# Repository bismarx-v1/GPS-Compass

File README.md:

# GPS Compass
this compass points to a specific locations a user defines, it has two pointers, one for distance and another one for the specified locations

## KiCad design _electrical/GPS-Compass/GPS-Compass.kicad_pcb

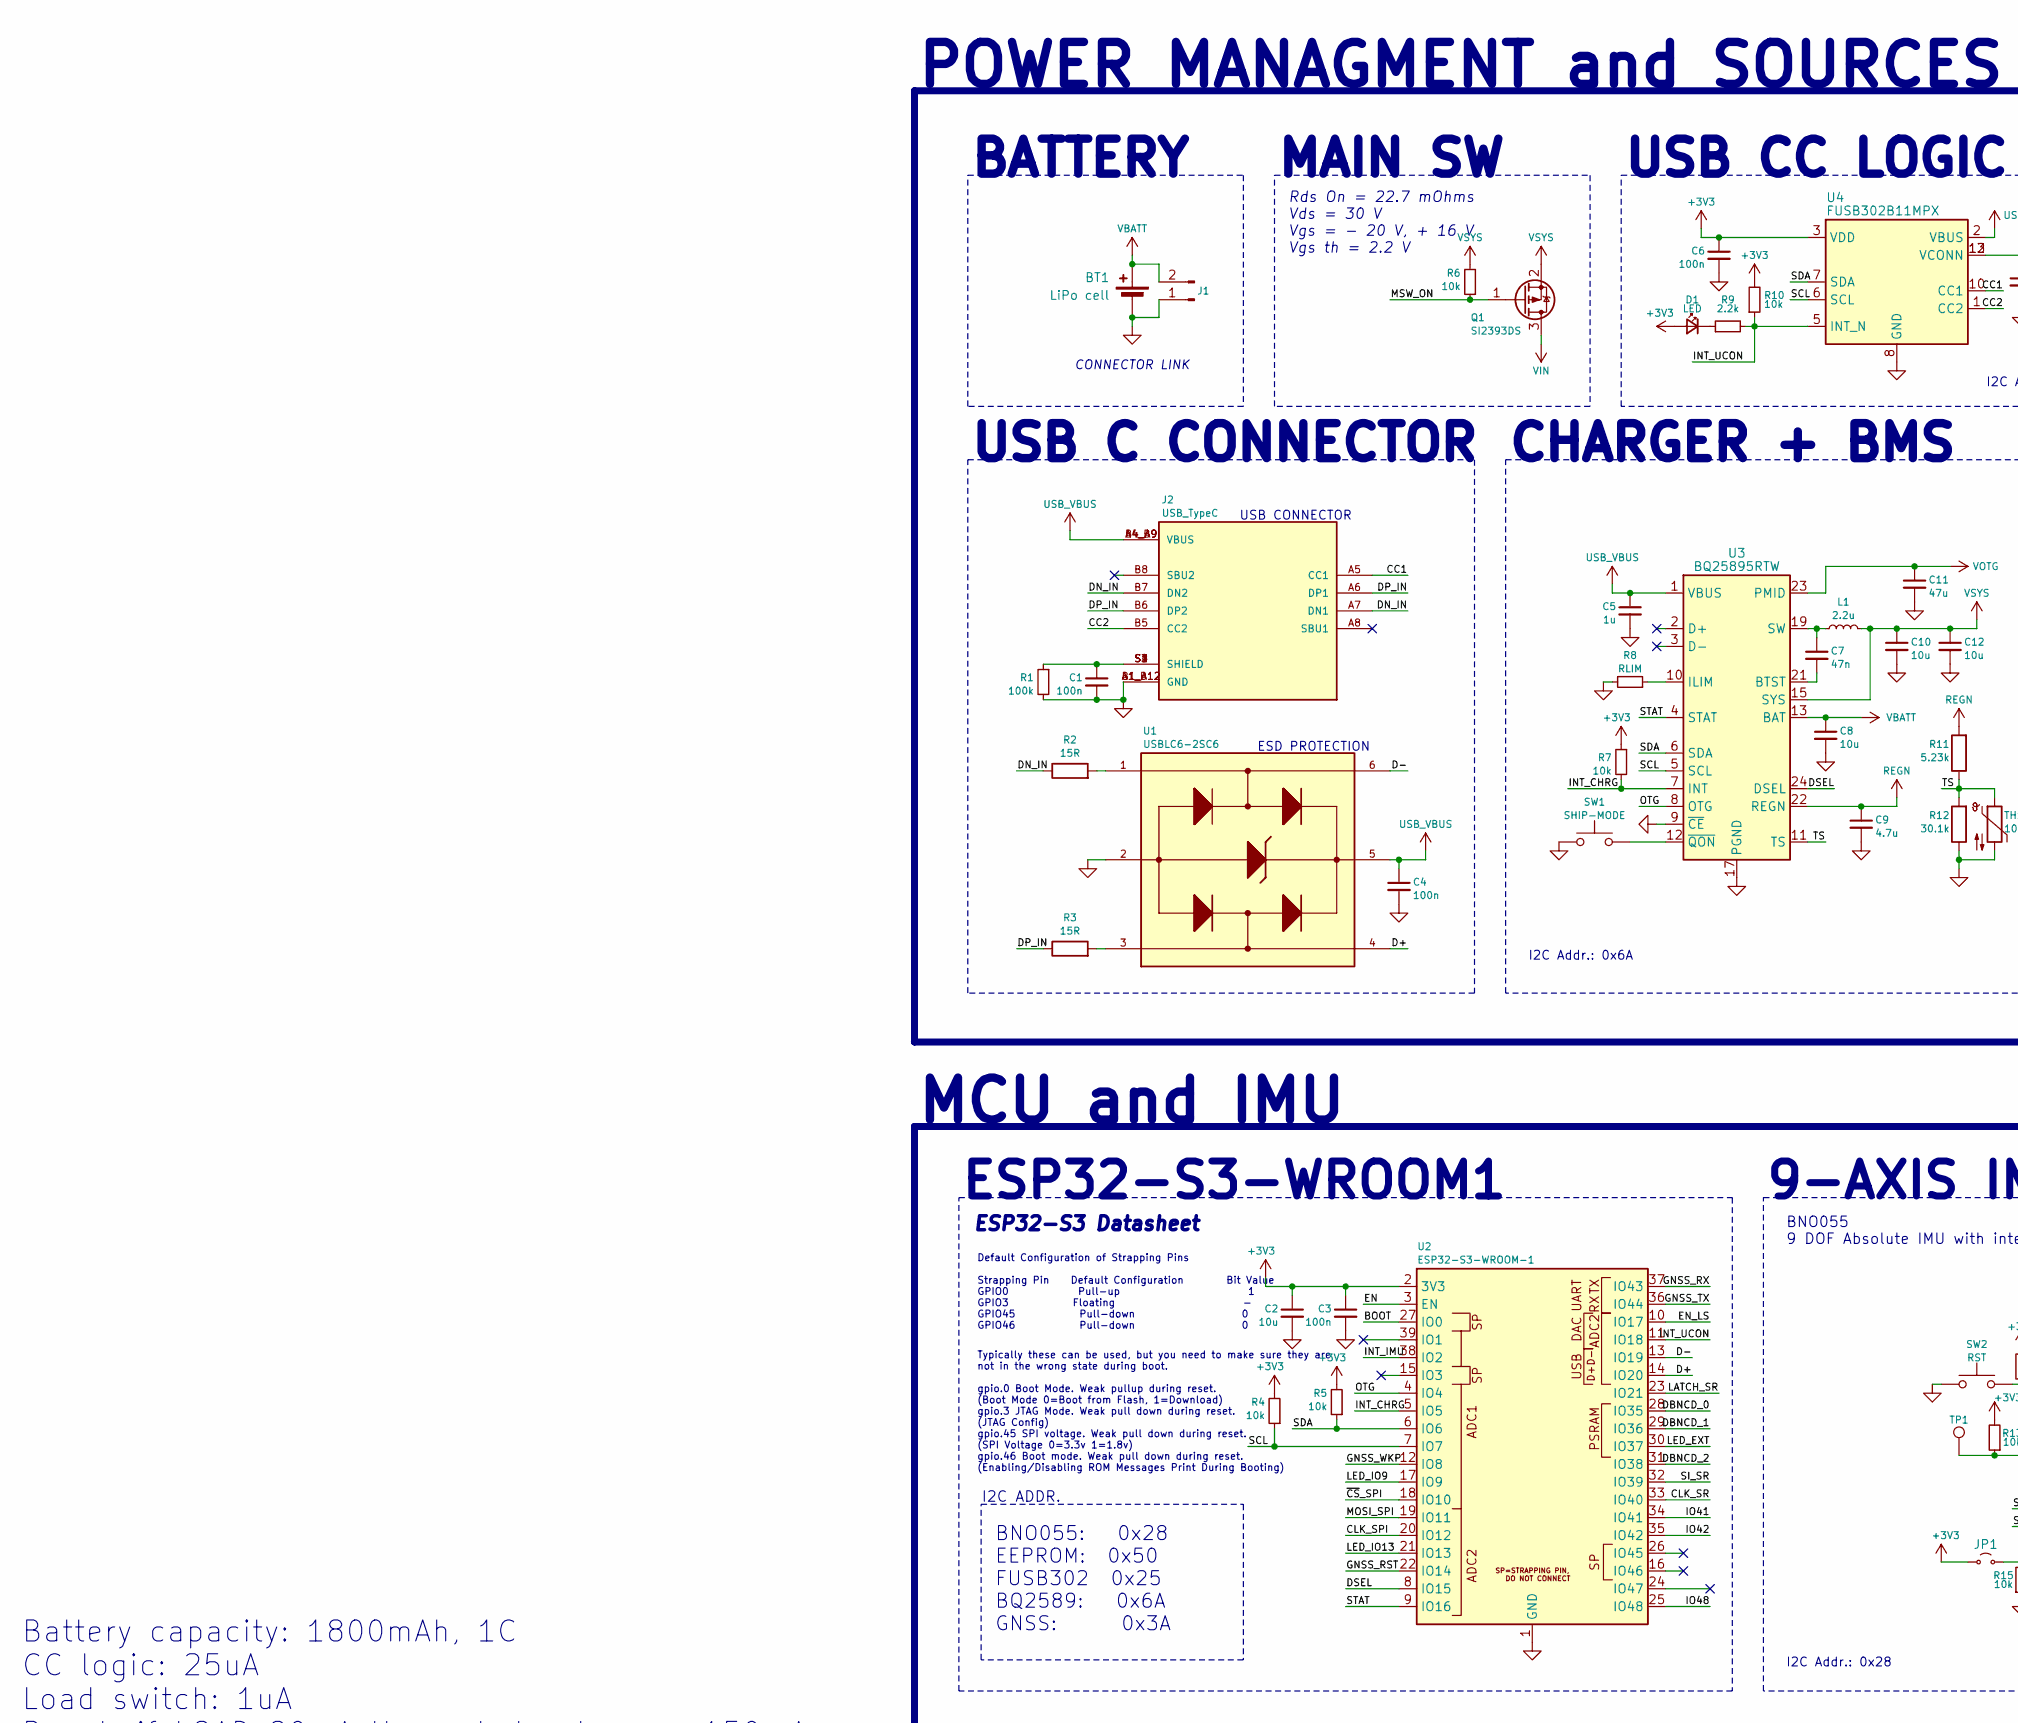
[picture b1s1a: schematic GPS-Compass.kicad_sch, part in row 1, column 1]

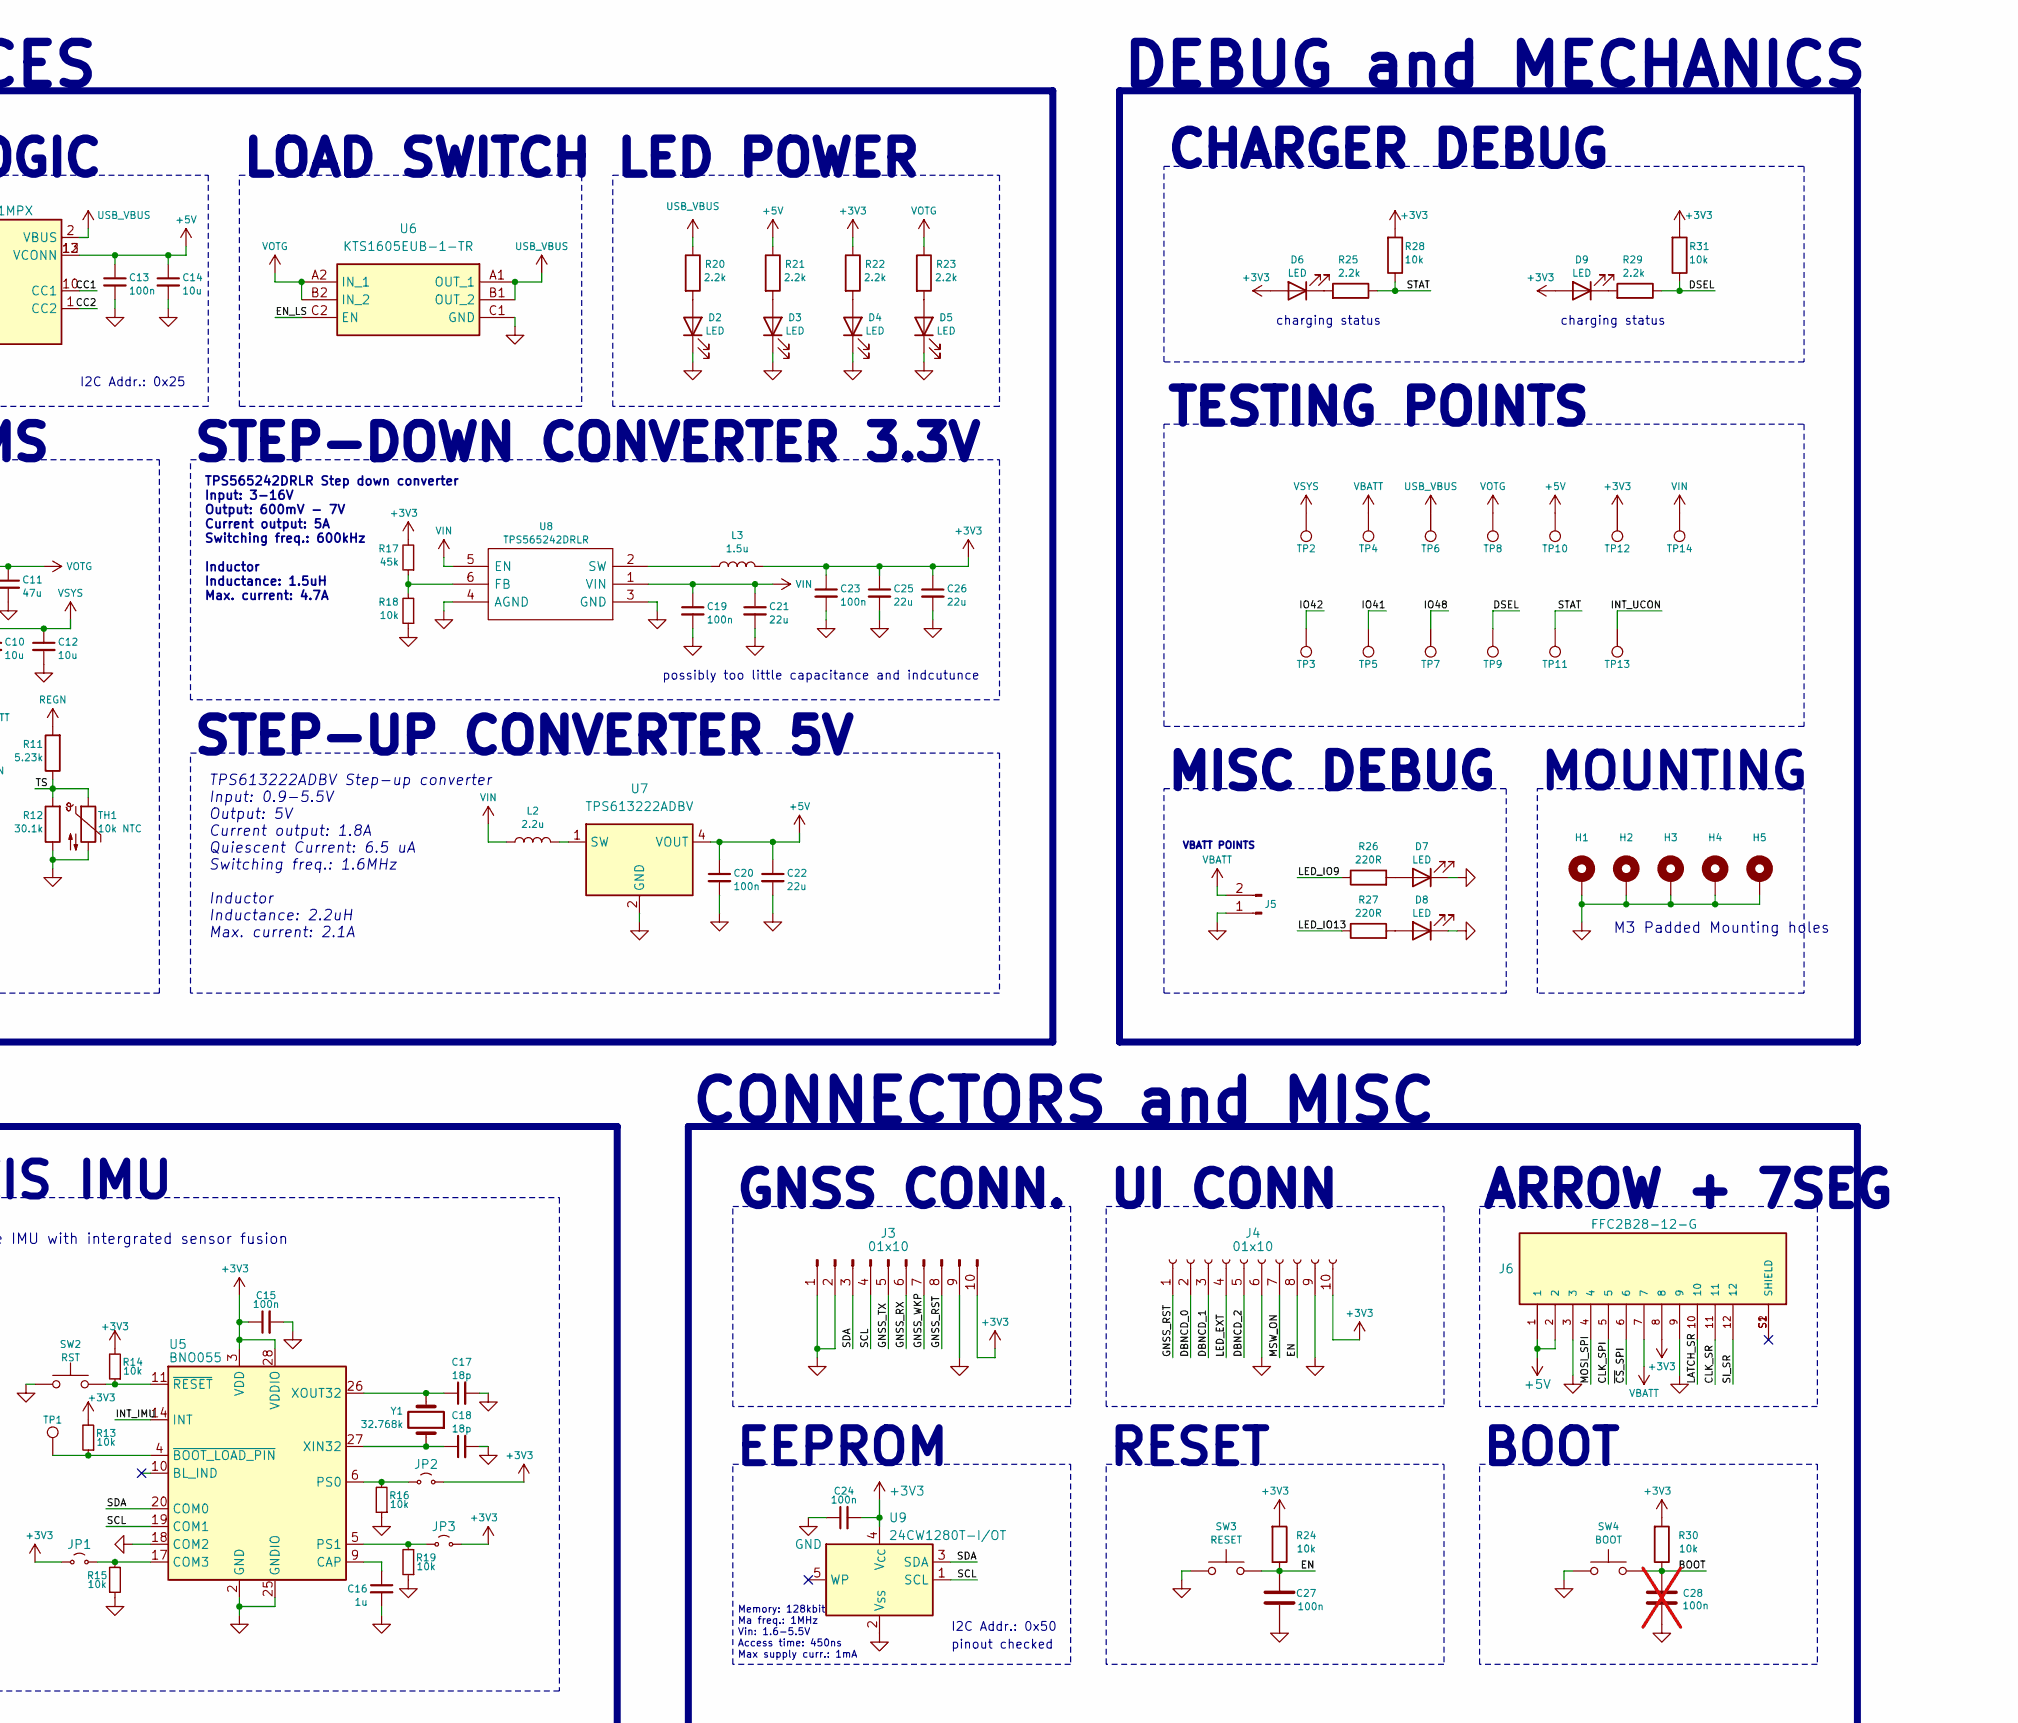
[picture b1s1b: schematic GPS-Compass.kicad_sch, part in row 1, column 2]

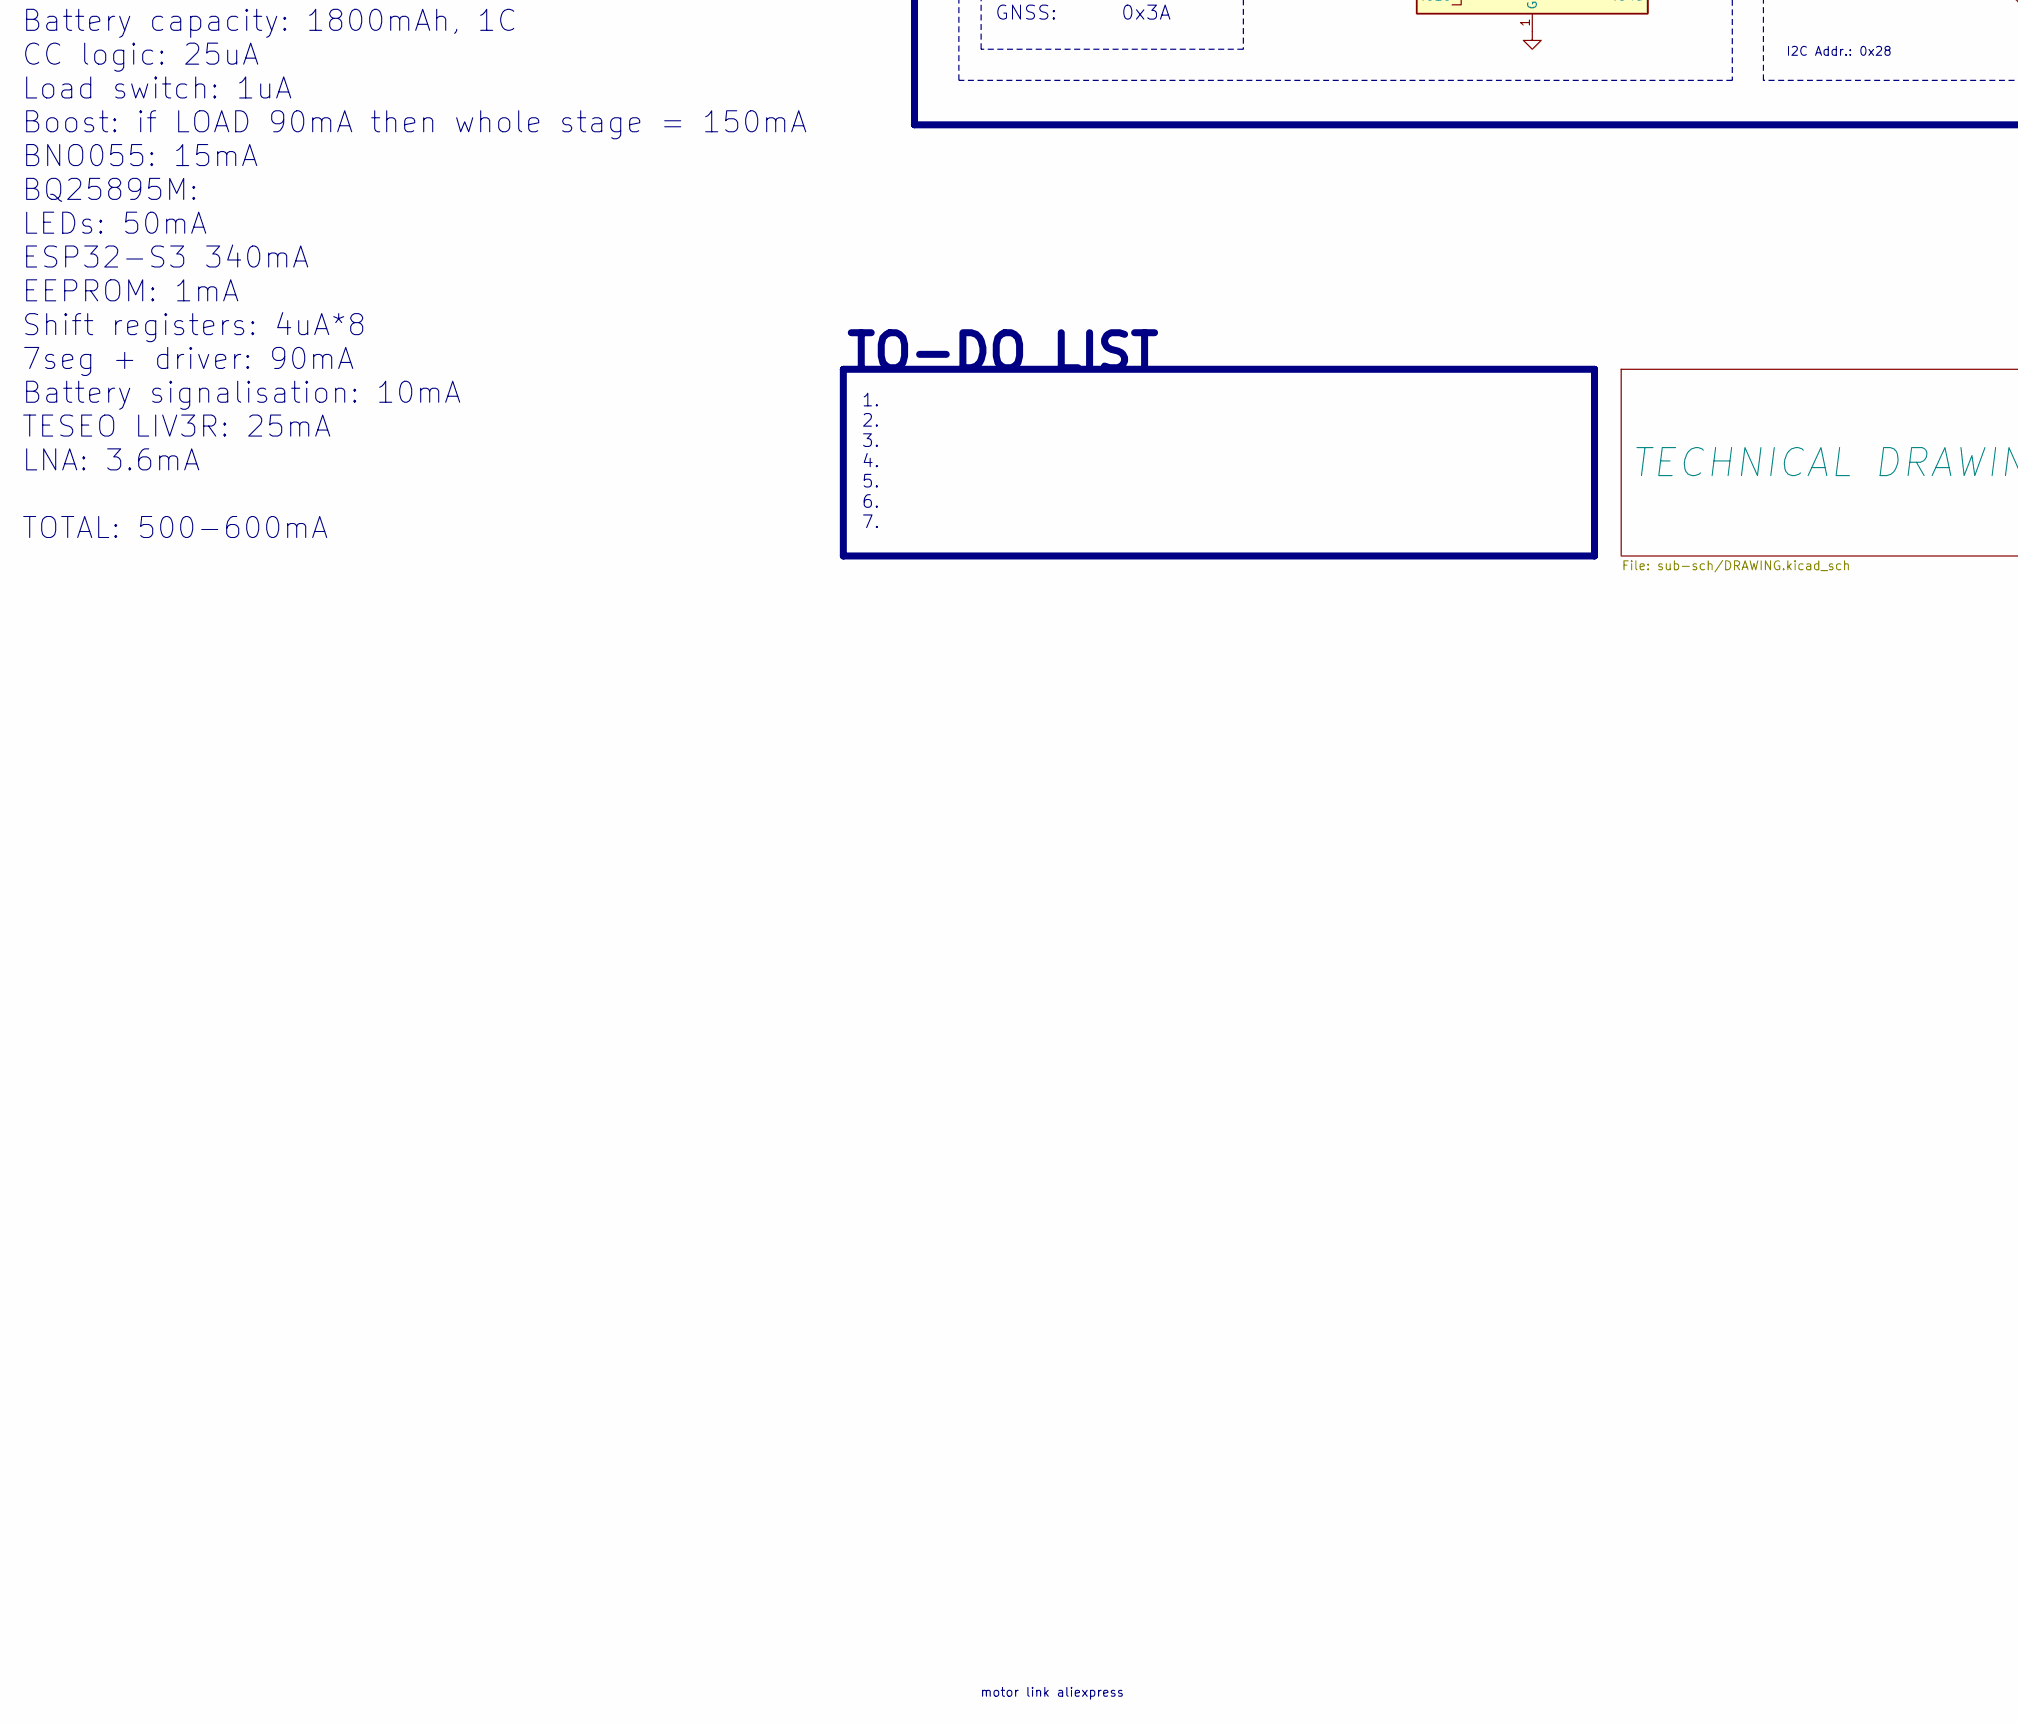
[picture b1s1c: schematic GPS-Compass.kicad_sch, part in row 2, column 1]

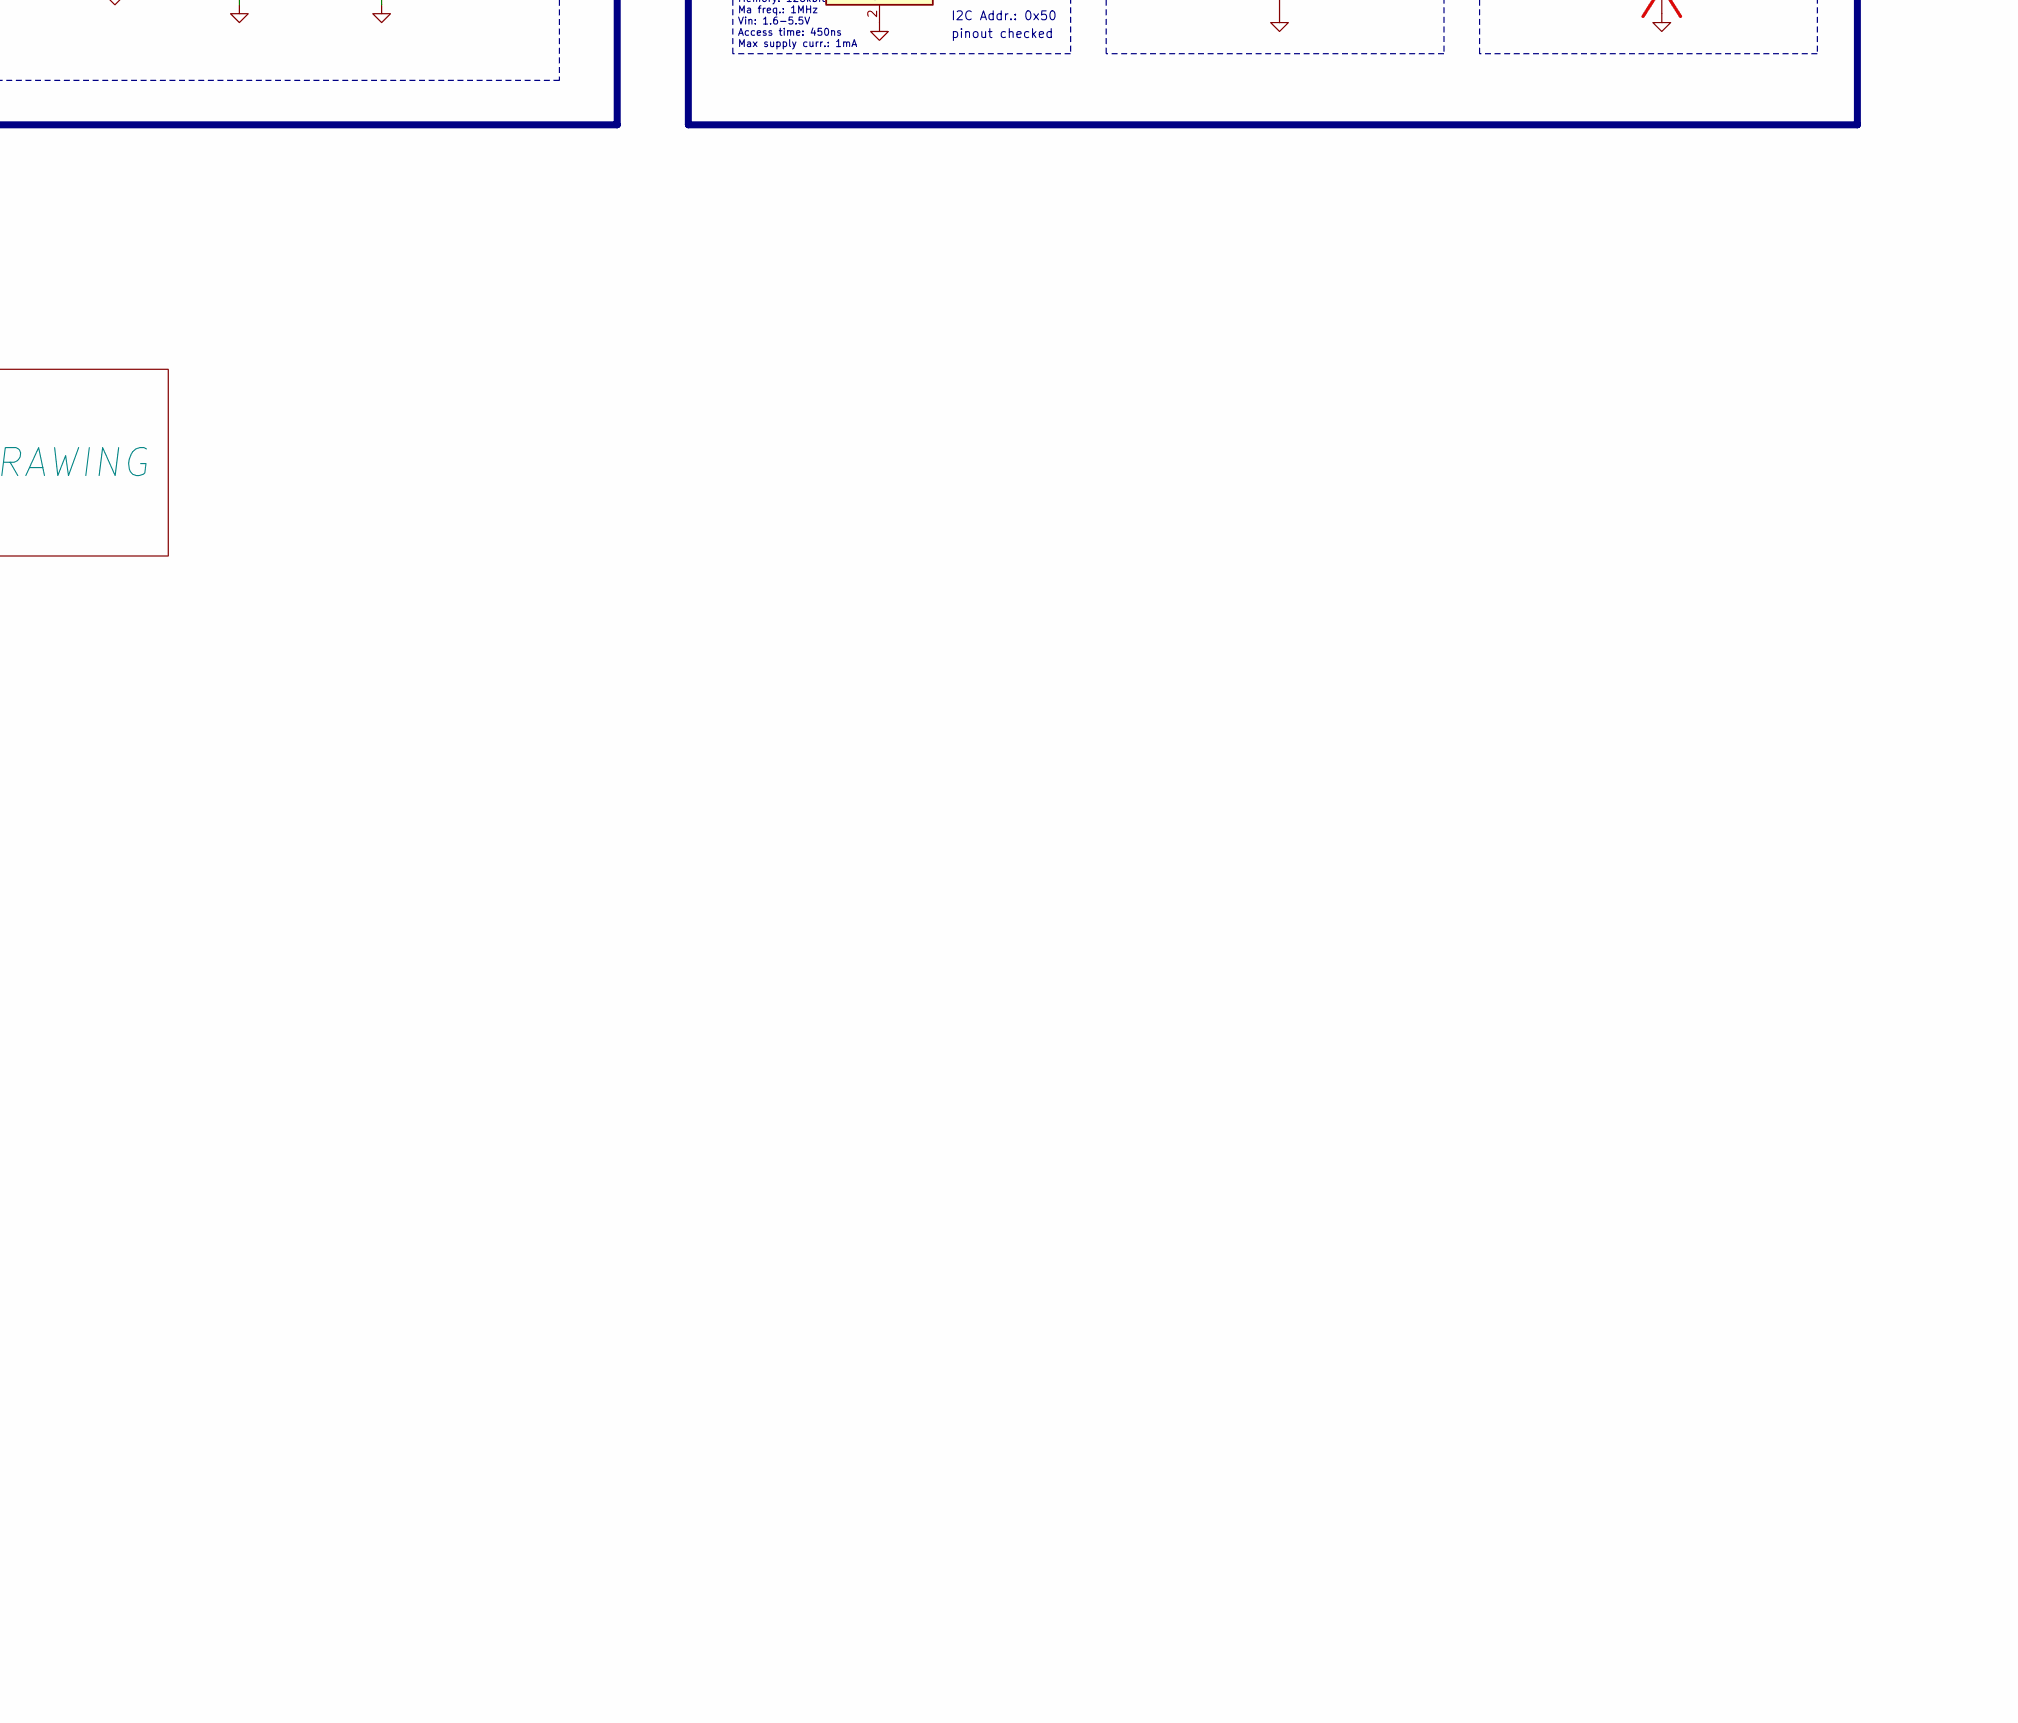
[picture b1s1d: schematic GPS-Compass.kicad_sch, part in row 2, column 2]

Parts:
BT1: LiPo cell
C1, C3, C4, C6, C13, C15, C19, C20, C23, C24, C27: 100n; C_0805_2012Metric
C2, C8, C10, C12, C14: 10u; C_0805_2012Metric
C5, C16: 1u; C_0805_2012Metric
C7: 47n; C_0805_2012Metric
C9: 4.7u; C_0805_2012Metric
C11: 47u; C_1210_3225Metric
C17, C18: 18p; C_0805_2012Metric
C21, C22, C25, C26: 22u; C_0805_2012Metric
C28: 100n; C_0805_2012Metric; not fitted
D1, D2, D3, D4, D5, D6, D7, D8, D9: LED; LED_0805_2012Metric
H1, H2, H3, H4, H5: Mounting Hole M3; MountingHole_3.2mm_M3_Pad_Via
J1: Conn_01x02_Pin; JST_PH_S2B-PH-K_1x02_P2.00mm_Horizontal
J2: USB_TypeC; HRO_TYPE-C-31-M-12; PARTREV 2020.12.08
J3, J4: 01x10; PinSocket_1x10_P2.54mm_Horizontal
J5: Conn_01x02_Pin; SolderWire-0.1sqmm_1x02_P3.6mm_D0.4mm_OD1mm
J6: FFC2B28-12-G; GCT_FFC2B28-12-G; PARTREV A
JP1, JP2, JP3: Jumper_2_Small_Open; SolderJumper-2_P1.3mm_Open_RoundedPad1.0x1.5mm
L1, L2: 2.2u; L_1008_2520Metric
L3: 1.5u; L_Vishay_IHLP-1212
Q1: SI2393DS; SOT-23-3
R1: 100k; R_0805_2012Metric
R2, R3: 15R; R_0805_2012Metric
R4, R5, R6, R7, R10, R13, R14, R15, R16, R18, R19, R24, R30: 10k; R_0805_2012Metric
R8: RLIM; R_0805_2012Metric
R9: 2.2k; R_0805_2012Metric
R11: 5.23k; R_0805_2012Metric; LCSC C17633
R12: 30.1k; R_0805_2012Metric; LCSC C17633
R17: 45k; R_0805_2012Metric
R20, R21, R22, R23, R25, R29: 2.2k; R_0805_2012Metric; LCSC C17633
R26, R27: 220R; R_0805_2012Metric; LCSC C17633
R28, R31: 10k; R_0805_2012Metric; LCSC C17633
SW1: SHIP-MODE; SW_SPST_EVQPE1
SW2: RST; SW_SPST_EVQPE1
SW3: RESET; SW_SPST_EVQPE1
SW4: BOOT; SW_SPST_EVQPE1
TH1: 10k NTC; R_0805_2012Metric
TP1, TP2, TP3, TP4, TP5, TP6, TP7, TP8, TP9, TP10, TP11, TP12, TP13, TP14: TestPoint; TestPoint_Pad_D1.0mm
U1: USBLC6-2SC6; TSOT-23-6_HandSoldering
U2: ESP32-S3-WROOM-1
U3: BQ25895RTW; Texas_RTW_WQFN-24-1EP_4x4mm_P0.5mm_EP2.7x2.7mm_ThermalVias
U4: FUSB302B11MPX; WQFN-14-1EP_2.5x2.5mm_P0.5mm_EP1.45x1.45mm
U5: BNO055; LGA-28_5.2x3.8mm_P0.5mm
U6: KTS1605EUB-1-TR; KTS1605EUB1TR; Manufacturer_Part_Number KTS1605EUB-1-TR
U7: TPS613222ADBV; SOT-23-5
U8: TPS565242DRLR; SOT-563; Manufacturer_Part_Number TPS565242DRLR; Mouser Part Number 595-TPS565242DRLR
U9: 24CW1280T-I/OT; SOT-23-5
Y1: 32.768k; CM8V32768TA020125

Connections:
+3V3: C2.1, C3.1, C6.1, C15.1, C23.1, C24.2, C25.1, C26.1, D1.2 (A), D6.2 (A), D9.2 (A), J3.10, J4.10, J6.8, JP1.2 (B), JP2.2 (B), JP3.2 (B), L3.2, R4.2, R5.2, R7.1, R10.2, R13.2, R14.2, R17.2, R22.1, R24.2, R28.2, R30.2, R31.2, TP12.1, U2.2 (3V3), U4.3 (VDD), U4.4 (VDD), U5.3 (VDD), U5.28 (VDDIO), U9.4 (V_{CC})
+5V: C13.1, C14.1, C20.1, C22.1, J6.1, J6.2, R21.1, TP10.1, U4.12 (VCONN), U4.13 (VCONN), U7.4 (VOUT)
/BOOT: C28.2, R30.1, SW4.2, U2.27 (IO0)
/CC1: J2.A5 (CC1), U4.10 (CC1), U4.11 (CC1)
/CC2: J2.B5 (CC2), U4.1 (CC2), U4.14 (CC2)
/CLK_SPI: J6.5, U2.20 (IO12)
/CLK_SR: J6.11, U2.33 (IO40)
/D+: U1.4, U2.14 (IO20)
/D-: U1.6, U2.13 (IO19)
/DBNCD_0: J4.2, U2.28 (IO35)
/DBNCD_1: J4.3, U2.29 (IO36)
/DBNCD_2: J4.5, U2.31 (IO38)
/DN_IN: J2.A7 (DN1), J2.B7 (DN2), R2.1
/DP_IN: J2.A6 (DP1), J2.B6 (DP2), R3.1
/DSEL: R29.1, R31.1, TP9.1, U2.8 (IO15), U3.24 (DSEL)
/EN: C27.2, J4.8, R24.1, SW3.2, U2.3 (EN)
/EN_LS: U2.10 (IO17), U6.C2 (EN)
/GNSS_RST: J3.8, J4.1, U2.22 (IO14)
/GNSS_RX: J3.6, U2.37 (IO43)
/GNSS_TX: J3.5, U2.36 (IO44)
/GNSS_WKP: J3.7, U2.12 (IO8)
/INT_CHRG: R7.2, U2.5 (IO5), U3.7 (INT)
/INT_IMU: U2.38 (IO2), U5.14 (INT)
/INT_UCON: R9.2, R10.1, TP13.1, U2.11 (IO18), U4.5 (INT_N)
/IO41: TP5.1, U2.34 (IO41)
/IO42: TP3.1, U2.35 (IO42)
/IO48: TP7.1, U2.25 (IO48)
/LATCH_SR: J6.10, U2.23 (IO21)
/LED_EXT: J4.4, U2.30 (IO37)
/LED_IO9: R26.1, U2.17 (IO9)
/LED_IO13: R27.1, U2.21 (IO13)
/MOSI_SPI: J6.4, U2.19 (IO11)
/MSW_ON: J4.7, Q1.1 (G), R6.1
/OTG: U2.4 (IO4), U3.8 (OTG)
/SCL: J3.4, R4.1, U2.7 (IO7), U3.5 (SCL), U4.6 (SCL), U5.19 (COM1), U9.1 (SCL)
/SDA: J3.3, R5.1, U2.6 (IO6), U3.6 (SDA), U4.7 (SDA), U5.20 (COM0), U9.3 (SDA)
/SI_SR: J6.12, U2.32 (IO39)
/STAT: R25.1, R28.1, TP11.1, U2.9 (IO16), U3.4 (STAT)
/TS: R11.1, R12.2, TH1.1, U3.11 (TS)
/~CS_SPI: J6.6, U2.18 (IO10)
GND: BT1.2 (-), C1.2, C2.2, C3.2, C4.2, C5.2, C6.2, C8.2, C9.2, C10.2, C11.2, C12.2, C13.2, C14.2, C15.2, C16.2, C17.2, C18.2, C19.2, C20.2, C21.2, C22.2, C23.2, C24.1, C25.2, C26.2, C27.1, C28.1, D2.1 (K), D3.1 (K), D4.1 (K), D5.1 (K), D7.1 (K), D8.1 (K), H1.1, H2.1, H3.1, H4.1, H5.1, J1.1, J2.A1_B12 (GND), J2.B1_A12 (GND), J3.1, J3.2, J3.9, J4.6, J4.9, J5.1, J6.3, J6.9, R1.2, R8.2, R12.1, R15.1, R16.1, R18.1, R19.1, SW1.1, SW2.1, SW3.1, SW4.1, TH1.2, U1.2, U2.1 (GND), U2.40 (GND), U2.41 (GND), U3.9 (~CE), U3.17 (PGND), U3.18 (PGND), U3.25 (PGND), U4.8 (GND), U4.9 (GND), U4.15 (GND), U5.2 (GND), U5.18 (COM2), U5.25 (GNDIO), U6.C1 (GND), U7.2 (GND), U8.3 (GND), U8.4 (AGND), U9.2 (V_{SS})
unnamed: C1.1, J2.S1 (SHIELD), J2.S2 (SHIELD), J2.S3 (SHIELD), J2.S4 (SHIELD), R1.1
unnamed: C7.1, L1.1, U3.19 (SW), U3.20 (SW)
unnamed: D1.1 (K), R9.1
unnamed: D2.2 (A), R20.2
unnamed: D3.2 (A), R21.2
unnamed: D4.2 (A), R22.2
unnamed: D5.2 (A), R23.2
unnamed: D6.1 (K), R25.2
unnamed: D7.2 (A), R26.2
unnamed: D8.2 (A), R27.2
unnamed: D9.1 (K), R29.2
unnamed: JP1.1 (A), R15.2, U5.17 (COM3)
unnamed: JP2.1 (A), R16.2, U5.6 (PS0)
unnamed: JP3.1 (A), R19.2, U5.5 (PS1)
unnamed: R2.2, U1.1
unnamed: R3.2, U1.3
unnamed: C7.2, U3.21 (BTST)
unnamed: R8.1, U3.10 (ILIM)
unnamed: SW1.2, U3.12 (~QON)
unnamed: C16.1, U5.9 (CAP)
unnamed: C18.1, U5.27 (XIN32), Y1.1
unnamed: C17.1, U5.26 (XOUT32), Y1.2
unnamed: R13.1, TP1.1, U5.4 (~BOOT_LOAD_PIN)
unnamed: R14.1, SW2.2, U5.11 (~RESET)
unnamed: L2.2, U7.1 (SW)
unnamed: R17.1, R18.2, U8.6 (FB)
unnamed: L3.1, U8.2 (SW)
REGN: C9.1, R11.2, U3.22 (REGN)
USB_VBUS: C4.1, C5.1, J2.A4_B9 (VBUS), J2.B4_A9 (VBUS), R20.1, TP6.1, U1.5, U3.1 (VBUS), U4.2 (VBUS), U6.A1 (OUT_1), U6.B1 (OUT_2)
VBATT: BT1.1 (+), C8.1, J1.2, J5.2, J6.7, TP4.1, U3.13 (BAT), U3.14 (BAT)
VIN: C19.1, C21.1, L2.1, Q1.3 (D), TP14.1, U8.1 (VIN), U8.5 (EN)
VOTG: C11.1, R23.1, TP8.1, U3.23 (PMID), U6.A2 (IN_1), U6.B2 (IN_2)
VSYS: C10.1, C12.1, L1.2, Q1.2 (S), R6.2, TP2.1, U3.15 (SYS), U3.16 (SYS)

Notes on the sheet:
9-AXIS IMU
ESD PROTECTION
ARROW + 7SEG
VBATT POINTS
MOUNTING
TPS613222ADBV Step-up converter Input: 0.9-5.5V Output: 5V Current output: 1.8A Quiescent Current: 6.5 uA Switching freq.: 1.6MHz Inductor Inductance: 2.2uH Max. current: 2.1A
M3 Padded Mounting holes
Battery capacity: 1800mAh, 1C CC logic: 25uA Load switch: 1uA Boost: if LOAD 90mA then whole stage = 150mA BNO055: 15mA BQ25895M: LEDs: 50mA ESP32-S3 340mA EEPROM: 1mA Shift registers: 4uA*8 7seg + driver: 90mA Battery signalisation: 10mA TESEO LIV3R: 25mA LNA: 3.6mA TOTAL: 500-600mA
motor link aliexpress
I2C ADDR.
ESP32-S3-WROOM1
EEPROM
USB CONNECTOR
TO-DO LIST
I2C Addr.: 0x28
MAIN SW
MISC DEBUG
LED POWER
1. 2. 3. 4. 5. 6. 7.
Default Configuration of Strapping Pins Strapping Pin Default Configuration Bit Value GPIO0 Pull-up 1 GPIO3 Floating - GPIO45 Pull-down 0 GPIO46 Pull-down 0
CONNECTORS and MISC
BNO055 9 DOF Absolute IMU with intergrated sensor fusion
pinout checked
CONNECTOR LINK
USB CC LOGIC
DEBUG and MECHANICS
BATTERY
UI CONN
STEP-UP CONVERTER 5V
I2C Addr.: 0x6A
MCU and IMU
charging status
STEP-DOWN CONVERTER 3.3V
ESP32-S3 Datasheet
LOAD SWITCH
TPS565242DRLR Step down converter Input: 3-16V Output: 600mV - 7V Current output: 5A Switching freq.: 600kHz Inductor Inductance: 1.5uH Max. current: 4.7A
CHARGER DEBUG
possibly too little capacitance and indcutunce
BNO055: 0x28 EEPROM: 0x50 FUSB302 0x25 BQ2589: 0x6A GNSS: 0x3A
TESTING POINTS

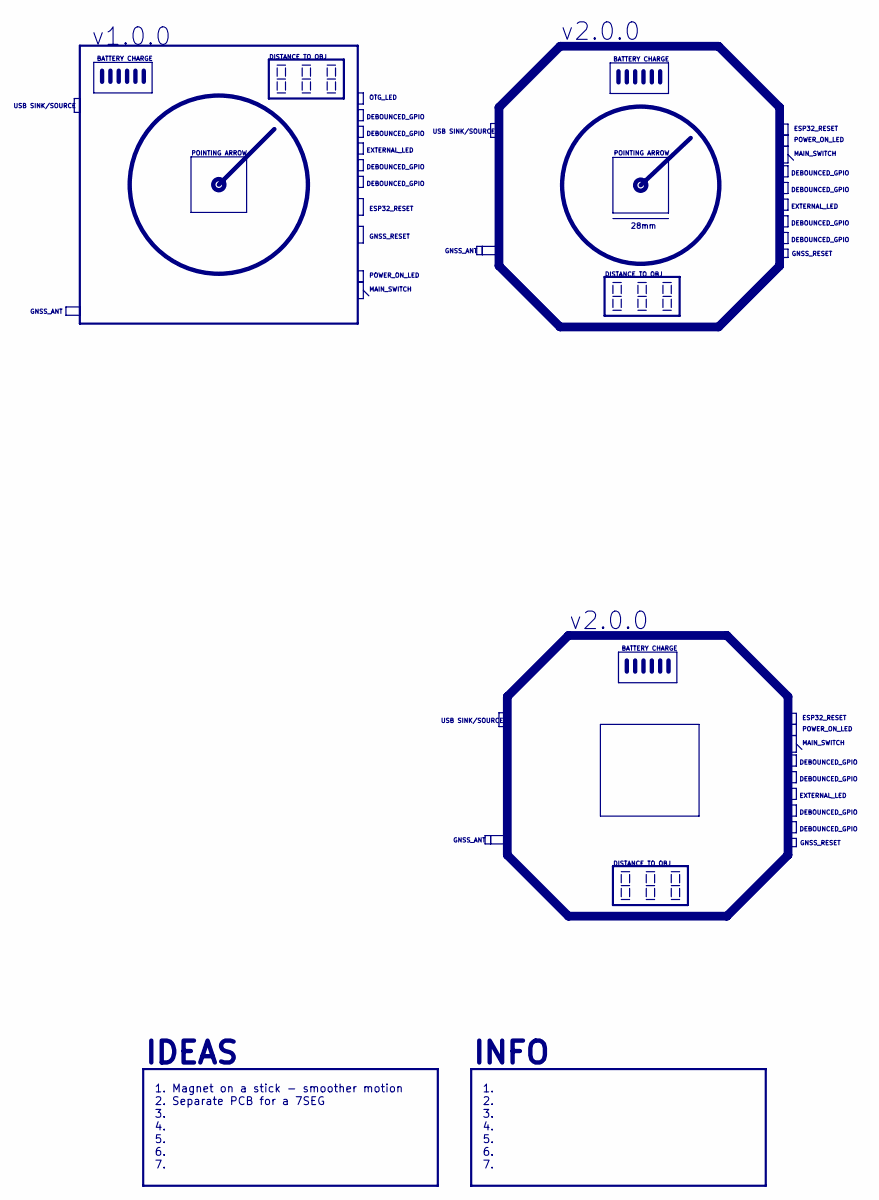
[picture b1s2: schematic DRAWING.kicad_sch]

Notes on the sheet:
DEBOUNCED_GPIO
28mm
USB SINK/SOURCE
EXTERNAL_LED
ESP32_RESET
IDEAS
1. 2. 3. 4. 5. 6. 7.
POINTING ARROW
GNSS_ANT
MAIN_SWITCH
DISTANCE TO OBJ
v2.0.0
v1.0.0
POWER_ON_LED
OTG_LED
BATTERY CHARGE
GNSS_RESET
INFO
1. Magnet on a stick - smoother motion 2. Separate PCB for a 7SEG 3. 4. 5. 6. 7.

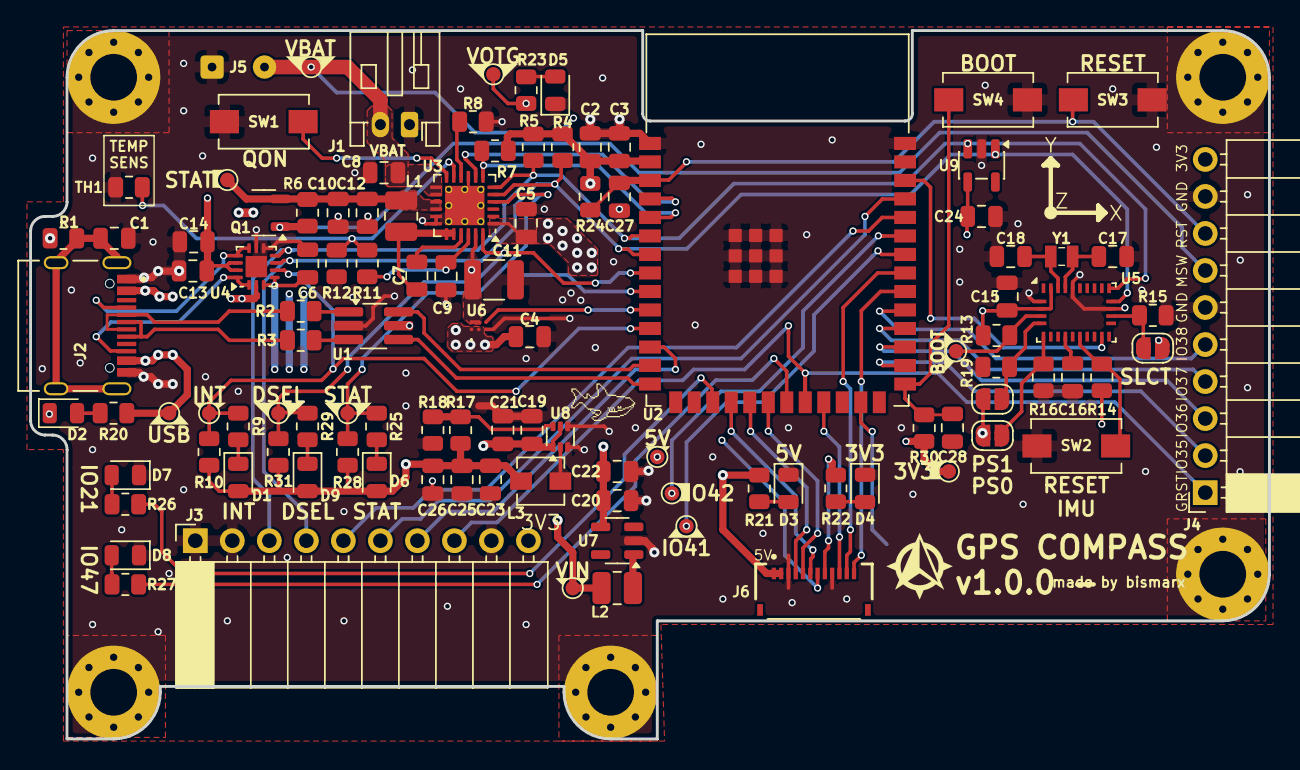
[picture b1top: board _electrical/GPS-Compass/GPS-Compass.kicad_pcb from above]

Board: 4 copper layers, 85.0 x 48.6 mm, 115 parts (1 on the bottom side), 74 nets.

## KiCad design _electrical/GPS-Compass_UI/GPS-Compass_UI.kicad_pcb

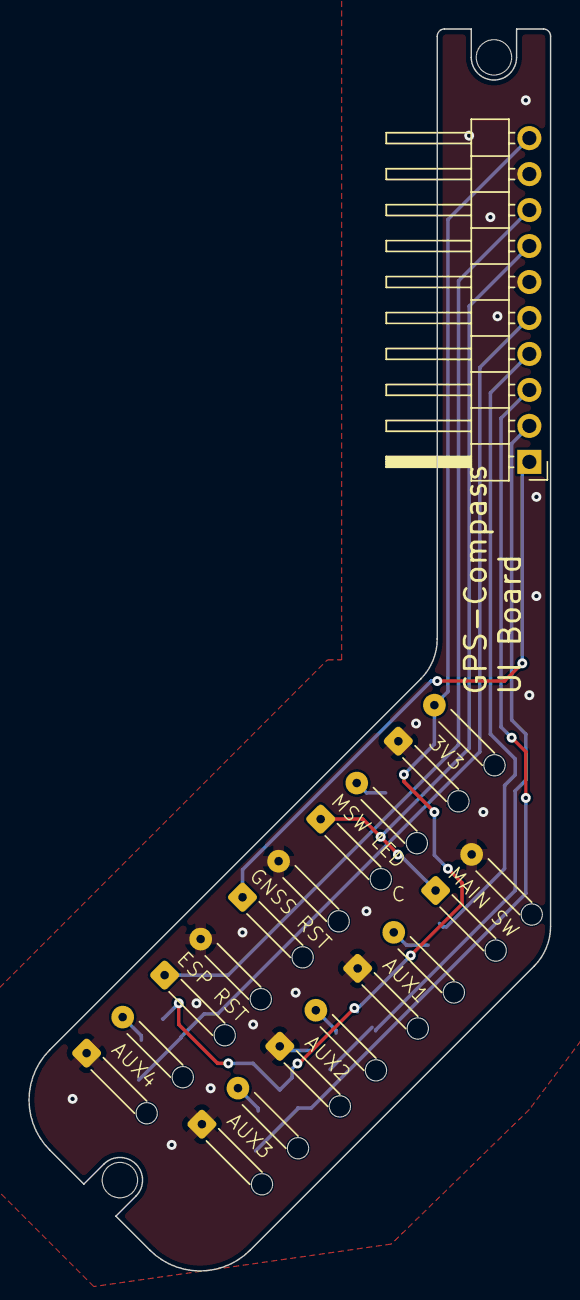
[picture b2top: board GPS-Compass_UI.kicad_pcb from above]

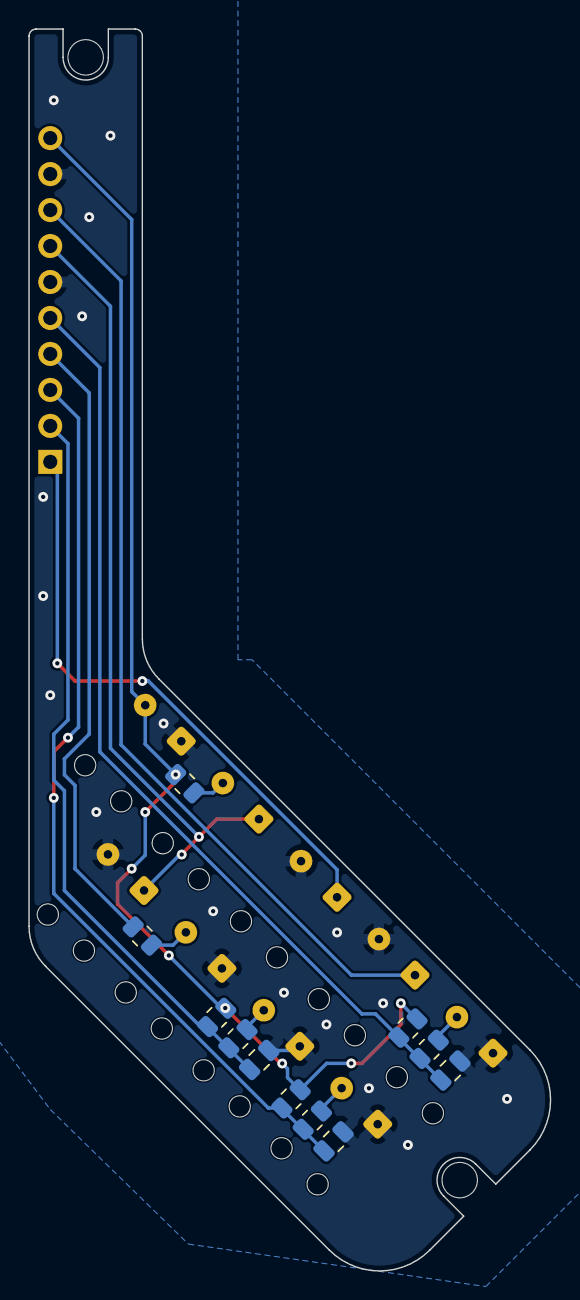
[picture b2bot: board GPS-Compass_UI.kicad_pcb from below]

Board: 2 copper layers, 36.8 x 87.7 mm, 23 parts (11 on the bottom side), 14 nets.

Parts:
C1: 100nF; C_0805_2012Metric
C2, C3: 100n; C_0805_2012Metric
D2, D3: LED; SolderWire-0.1sqmm_1x02_P3.6mm_D0.4mm_OD1mm_Relief
H1, H3: M2.5; MountingHole_2.5mm
J1: Conn_01x02_Pin; SolderWire-0.1sqmm_1x02_P3.6mm_D0.4mm_OD1mm_Relief
J4: Conn_01x10_Socket; PinHeader_1x10_P2.54mm_Horizontal
R1: 2.2k; R_0805_2012Metric
R3, R5, R8: 1k; R_0805_2012Metric
R4, R6, R9: 10k; R_0805_2012Metric
R7: 220R; R_0805_2012Metric
SW1: SPDT; SolderWire-0.1sqmm_1x02_P3.6mm_D0.4mm_OD1mm_Relief
SW3, SW5: RESET; SolderWire-0.1sqmm_1x02_P3.6mm_D0.4mm_OD1mm_Relief
SW4, SW6, SW7: EXT; SolderWire-0.1sqmm_1x02_P3.6mm_D0.4mm_OD1mm_Relief

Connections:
+3V3: J1.2, J4.10, R1.1, R4.2, R6.2, R9.2
/DBNCD_0: C1.2, J4.2, R3.2, R4.1
/DBNCD_1: C2.2, J4.3, R5.2, R6.1
/DBNCD_2: C3.2, J4.5, R8.2, R9.1
/DB_0: R3.1, SW4.2
/DB_1: R5.1, SW6.2
/DB_2: R8.1, SW7.2
/EN: J4.8, SW3.1
/GNSS_RST: J4.1, SW5.1
/LED_EXT: J4.4, R7.1
/MSW_ON: D2.1 (K), J4.7, SW1.1 (A)
GND: C1.1, C2.1, C3.1, D3.1 (K), J1.1, J4.6, J4.9, SW1.2 (B), SW3.2, SW4.1, SW5.2, SW6.1, SW7.1
unnamed: D2.2 (A), R1.2
unnamed: D3.2 (A), R7.2
